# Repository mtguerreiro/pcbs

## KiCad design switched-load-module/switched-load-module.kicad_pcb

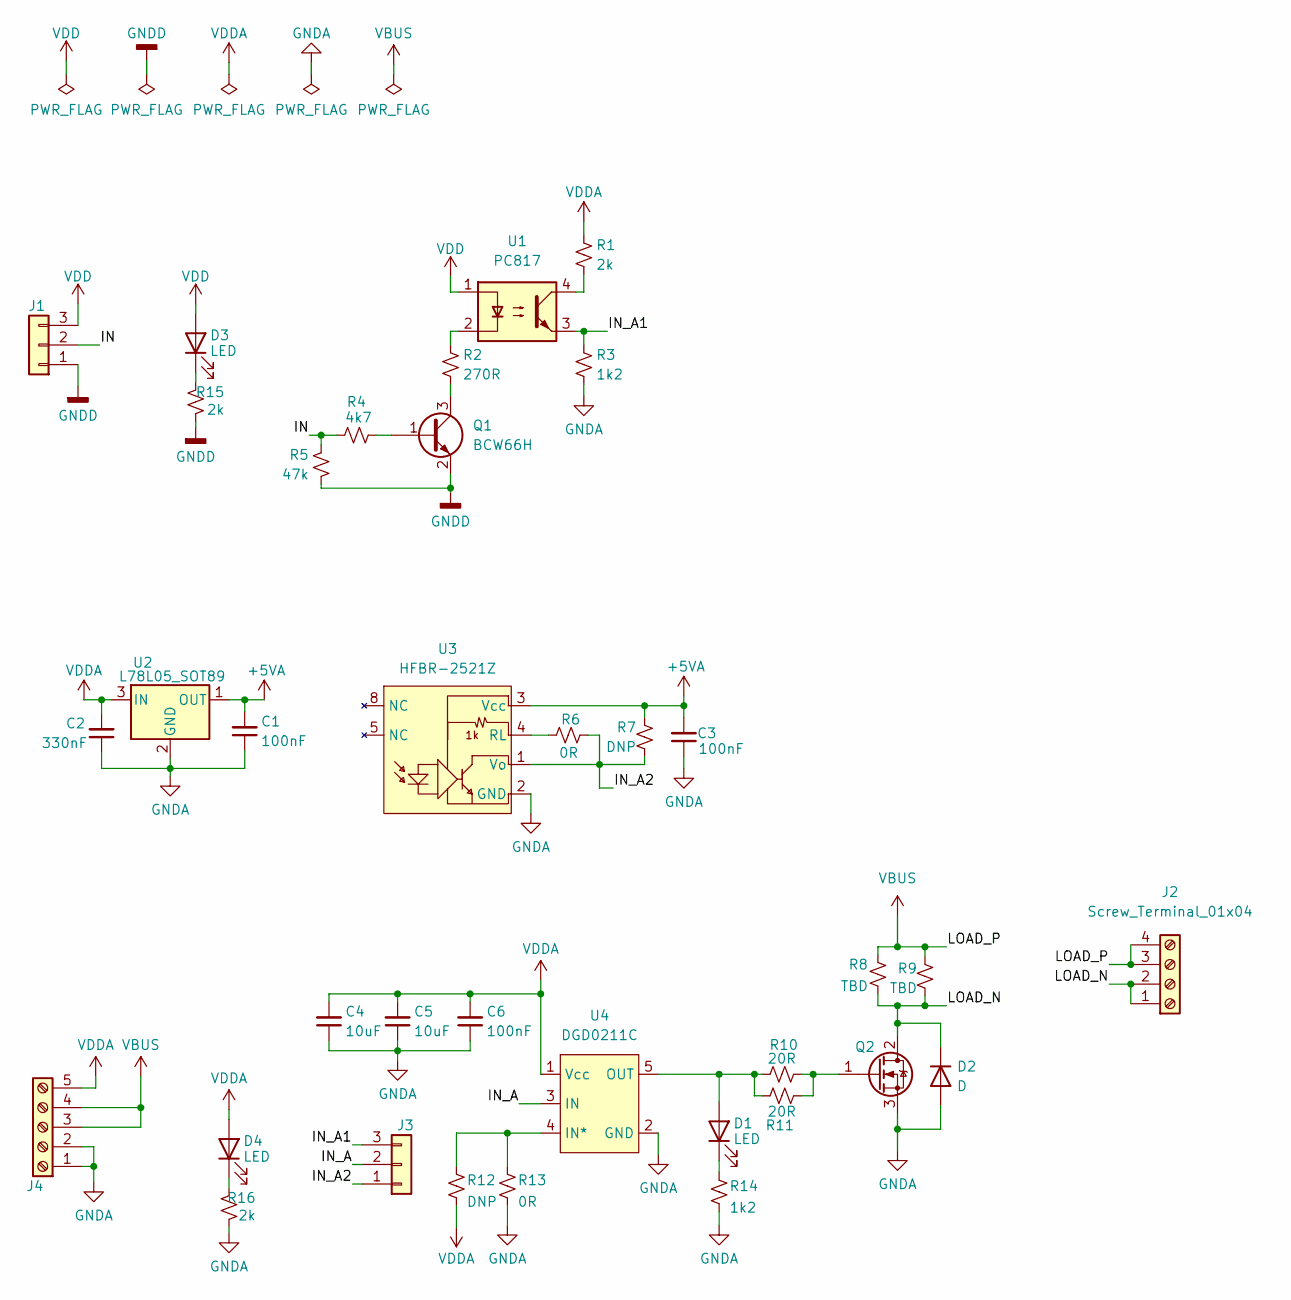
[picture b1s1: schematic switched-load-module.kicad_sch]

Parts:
C1, C3, C6: 100nF; C_0805_2012Metric_Pad1.18x1.45mm_HandSolder
C2: 330nF; C_0805_2012Metric_Pad1.18x1.45mm_HandSolder
C4, C5: 10uF; C_0805_2012Metric_Pad1.18x1.45mm_HandSolder
D1, D3, D4: LED; LED_0805_2012Metric_Pad1.15x1.40mm_HandSolder
D2: D; D_SMA
J1, J3: Conn_01x03; PinHeader_1x03_P2.54mm_Vertical
J2: Screw_Terminal_01x04; TerminalBlock_Phoenix_MKDS-1,5-4-5.08_1x04_P5.08mm_Horizont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
J4: Screw_Terminal_01x05; TerminalBlock_Phoenix_MKDS-1,5-5-5.08_1x05_P5.08mm_Horizont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
Q1: BCW66H; SOT-23W
Q2: Q_NMOS_GDS; TO-252-2
R1, R15, R16: 2k; R_0805_2012Metric_Pad1.20x1.40mm_HandSolder
R2: 270R; R_0805_2012Metric_Pad1.20x1.40mm_HandSolder
R3, R14: 1k2; R_0805_2012Metric_Pad1.20x1.40mm_HandSolder
R4: 4k7; R_0805_2012Metric_Pad1.20x1.40mm_HandSolder
R5: 47k; R_0805_2012Metric_Pad1.20x1.40mm_HandSolder
R6, R13: 0R; R_0805_2012Metric_Pad1.20x1.40mm_HandSolder
R7, R12: DNP; R_0805_2012Metric_Pad1.20x1.40mm_HandSolder
R8, R9: TBD; R_Axial_Power_L38.0mm_W9.0mm_P45.72mm
R10, R11: 20R; R_MELF_MMB-0207
U1: PC817; DIP-4_W8.89mm_SMDSocket_LongPads
U2: L78L05_SOT89; SOT-89-3
U3: HFBR-2521Z
U4: DGD0211C; TSOT-23-5_HandSoldering

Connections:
+5VA: C1.2, C3.2, R7.2, U2.1 (OUT), U3.3 (Vcc)
/IN: J1.2, R4.1, R5.2
/IN_A: J3.2, U4.3 (IN)
/IN_A1: J3.3, R3.1, U1.3
/IN_A2: J3.1, R6.1, R7.1, U3.1 (Vo)
/LOAD_N: D2.1 (K), J2.1, J2.2, Q2.2 (D), R8.1, R9.1
GNDA: C1.1, C2.1, C3.1, C4.1, C5.1, C6.1, D2.2 (A), J4.1, J4.2, Q2.3 (S), R3.2, R13.2, R14.2, R16.1, U2.2 (GND), U3.2 (GND), U4.2 (GND)
GNDD: J1.1, Q1.2 (E), R5.1, R15.1
unnamed: D1.1 (K), R14.1
unnamed: D1.2 (A), R10.1, R11.2, U4.5 (OUT)
unnamed: D3.1 (K), R15.2
unnamed: D4.1 (K), R16.2
unnamed: Q1.1 (B), R4.2
unnamed: Q1.3 (C), R2.2
unnamed: Q2.1 (G), R10.2, R11.1
unnamed: R1.2, U1.4
unnamed: R2.1, U1.2
unnamed: R6.2, U3.4 (RL)
unnamed: R12.1, R13.1, U4.4 (IN*)
VBUS: J2.3, J2.4, J4.3, J4.4, R8.2, R9.2
VDD: D3.2 (A), J1.3, U1.1
VDDA: C2.2, C4.2, C5.2, C6.2, D4.2 (A), J4.5, R1.1, R12.2, U2.3 (IN), U4.1 (Vcc)

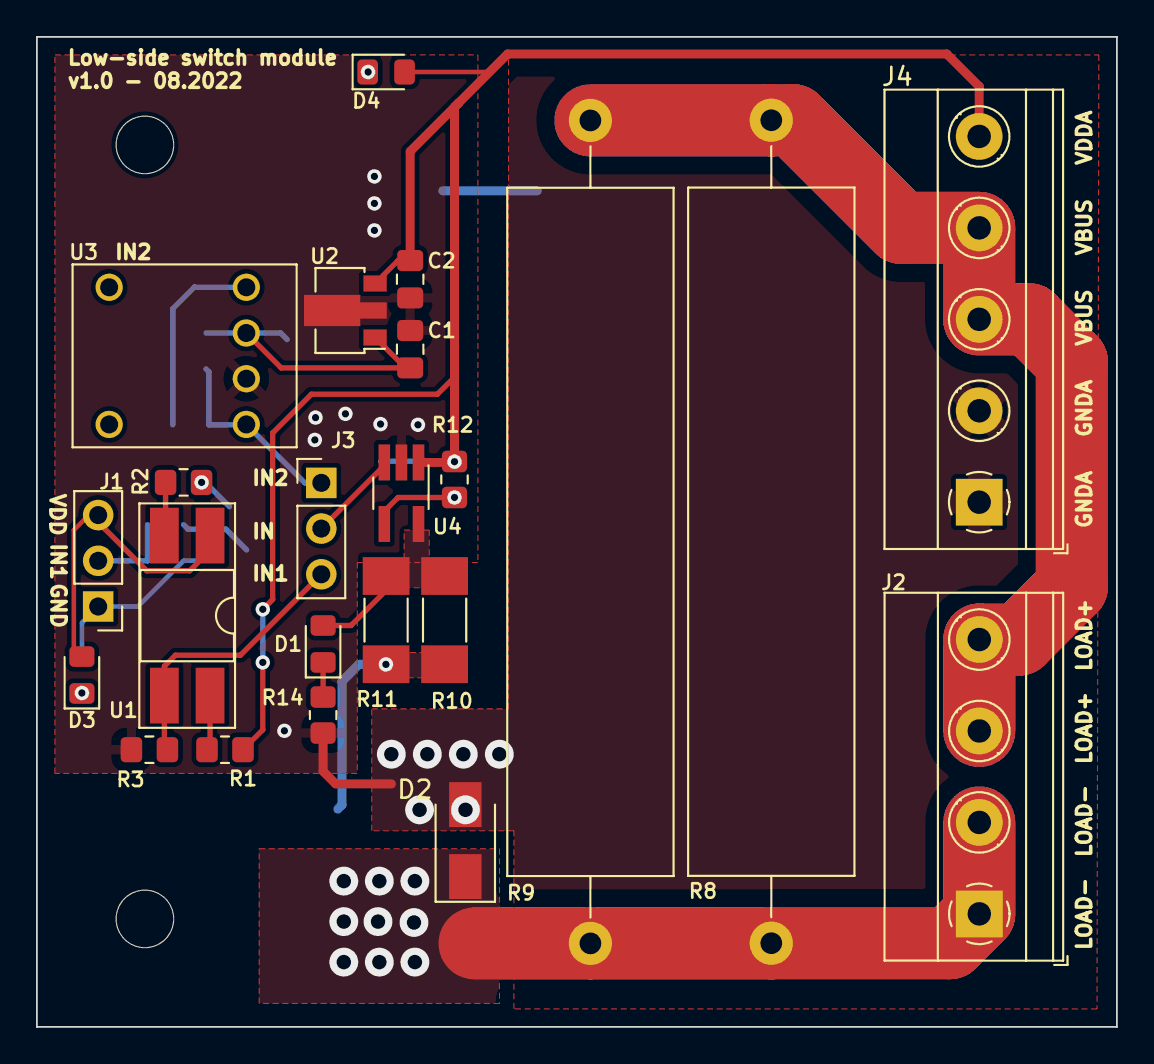
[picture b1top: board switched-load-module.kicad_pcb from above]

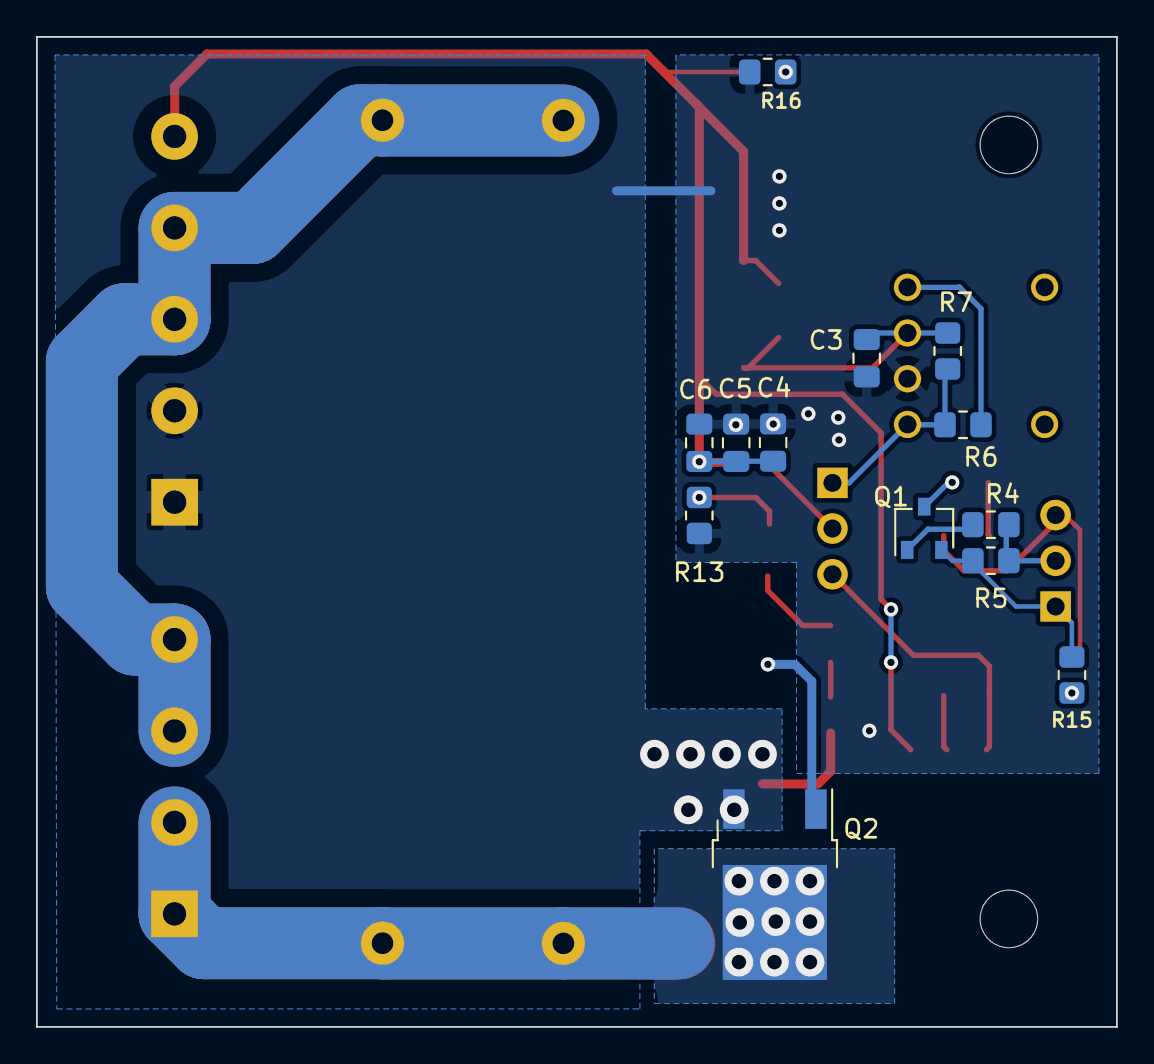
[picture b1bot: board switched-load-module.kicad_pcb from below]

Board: 2 copper layers, 60.0 x 55.0 mm, 36 parts (13 on the bottom side), 22 nets.
